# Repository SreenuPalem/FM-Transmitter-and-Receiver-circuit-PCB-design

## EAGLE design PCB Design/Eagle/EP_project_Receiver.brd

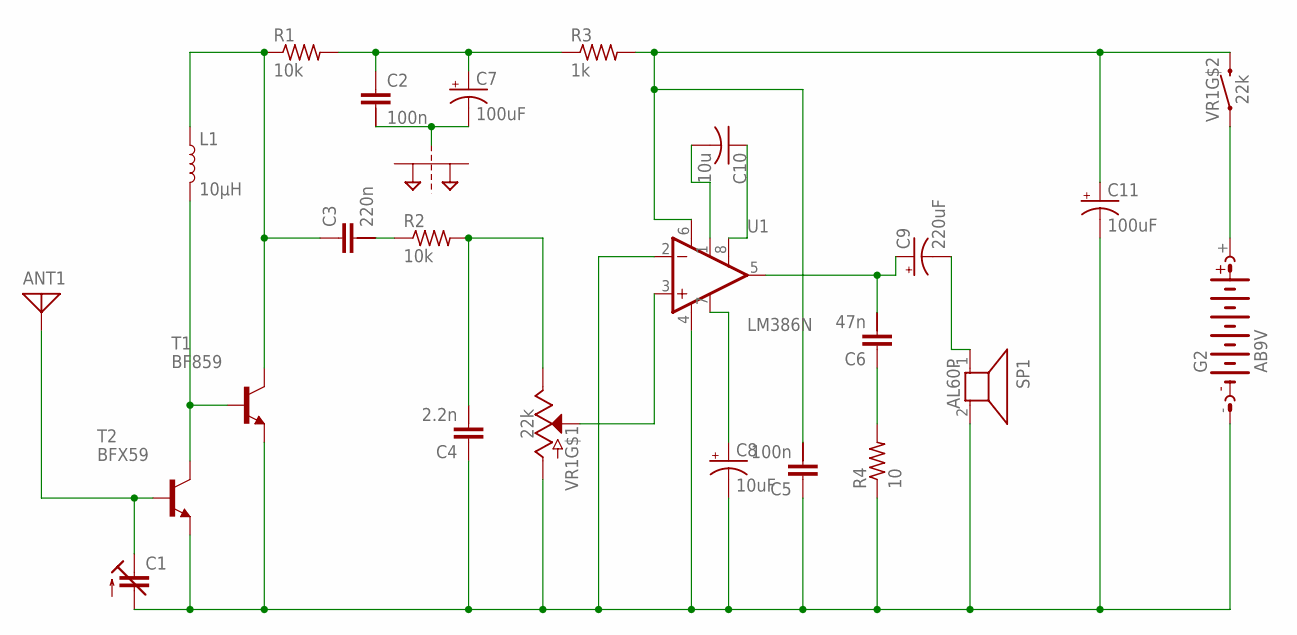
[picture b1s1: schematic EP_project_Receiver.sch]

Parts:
ANT1: ANTENNA; PAD-01
C1: C-TRIMM808; CTRIM808-BC
C2, C5: 100n; C2.5/5-5
C3: 220n; C2.5/5-5
C4: 2.2n; C2.5/5-5
C6: 47n; C2.5/5-5
C7, C11: 100uF; PANASONIC_G
C8: 10uF; PANASONIC_G
C9: 220uF; PANASONIC_G
C10: 10u; C025-024X044
G2: AB9V
L1: 10μH; 0805
R1, R2: 10k; 0204/7
R3: 1k; 0204/7
R4: 10; 0204/7
SP1: AL60P
SUPPLYTIE1: 2PT_GND_TIE
T1: BF859; TO202
T2: BFX59; TO72
U1: LM386N; DIP08
VR1: 22k; POT-SWITCH-PTH

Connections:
unnamed: ANT1.1, C1.1 (E), T2.2 (B)
unnamed: L1.2, T1.3 (B), T2.3 (C)
unnamed: C3.1, L1.1, R1.1, T1.2 (C)
unnamed: C3.2, R2.1
unnamed: C4.2, R2.2, VR1.3 (E)
unnamed: C1.2 (A), C4.1, C5.1, C8.-, C11.-, G2.-, R4.1, SP1.2, T1.1 (E), T2.1 (E), U1.2 (-IN), U1.4 (V-), VR1.1 (A)
unnamed: U1.3 (+IN), VR1.2 (S)
unnamed: C9.-, SP1.1
unnamed: C2.1, C7.+, R1.2, R3.1
unnamed: C2.2, C7.-
unnamed: C5.2, C11.+, R3.2, U1.6 (V+), VR1.S2 (2)
unnamed: G2.+, VR1.S1 (1)
unnamed: C6.1, R4.2
unnamed: C6.2, C9.+, U1.5 (OUT)
unnamed: C8.+, U1.7 (BP)
unnamed: C10.1, U1.8 (GAIN)
unnamed: C10.2, U1.1 (GAIN)

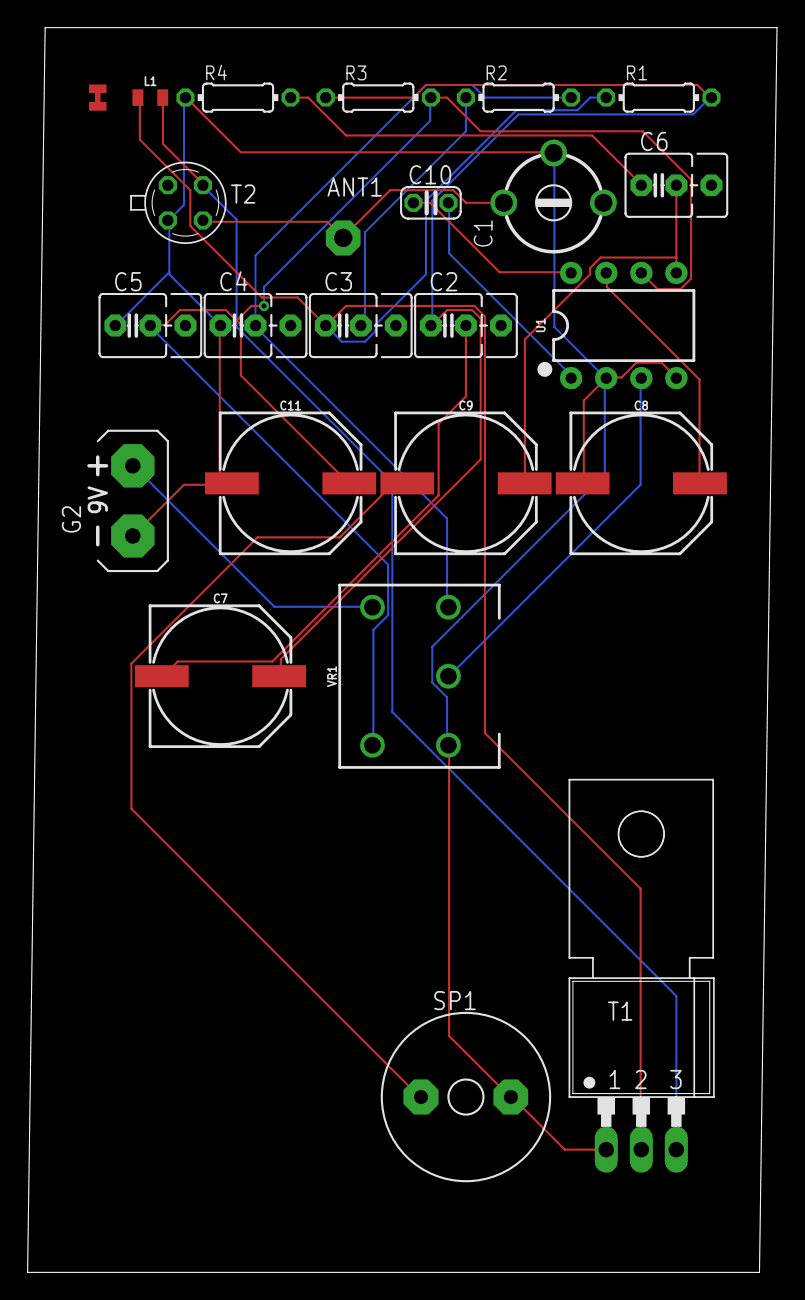
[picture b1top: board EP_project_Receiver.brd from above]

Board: 2 copper layers, 54.3 x 90.2 mm, 24 parts (0 on the bottom side), 17 nets.

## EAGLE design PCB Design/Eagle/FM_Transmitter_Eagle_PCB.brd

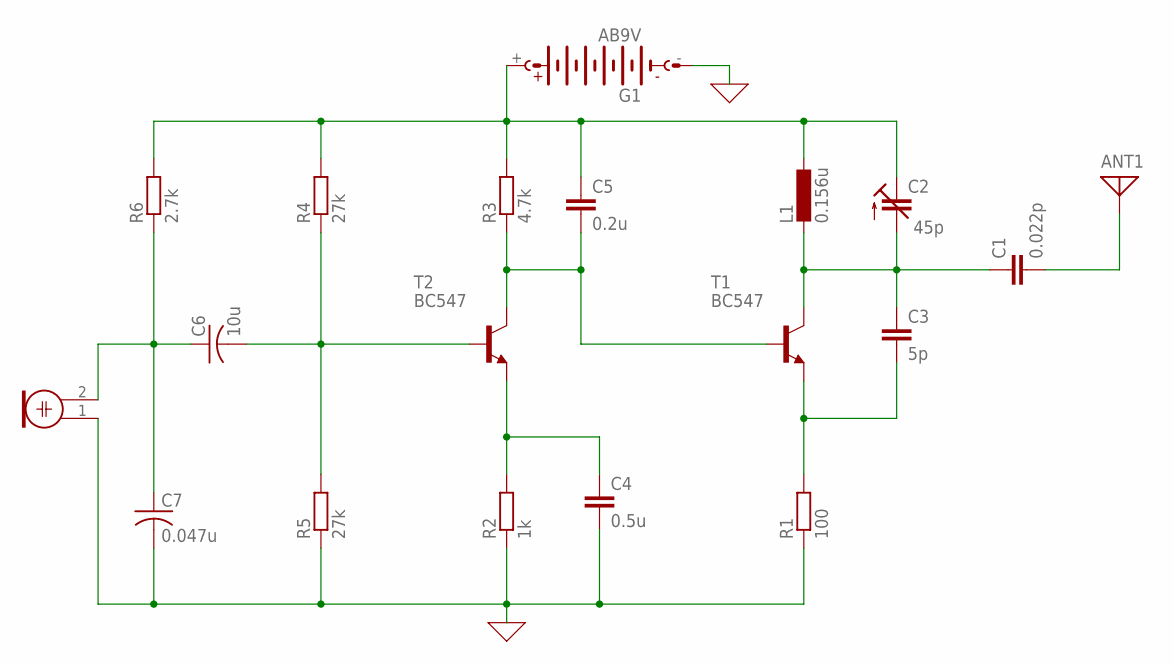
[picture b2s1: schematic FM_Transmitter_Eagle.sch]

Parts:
ANT1: ANTENNA; PAD-01
C1: 0.022p; C025-024X044
C2: 45p; CTRIM808-BC
C3: 5p; C025-024X044
C4: 0.5u; C025-024X044
C5: 0.2u; C025-024X044
C6: 10u; C025-024X044
C7: 0.047u; C025-024X044
G1: AB9V
L1: 0.156u; 0204/5
M1: ELECTRET_MICROPHON-F6050AP; F6050AP
R1: 100; 0204/7
R2: 1k; 0204/7
R3: 4.7k; 0204/7
R4, R5: 27k; 0204/7
R6: 2.7k; 0204/7
T1, T2: BC547; TO92

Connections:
0: C4.2, C7.2, G1.-, M1.1, R1.1, R2.1, R5.1
unnamed: ANT1.1, C1.2
unnamed: C6.1, C7.1, M1.2, R6.1
unnamed: C1.1, C2.2 (A), C3.1, L1.2, T1.3 (C)
unnamed: C3.2, R1.2, T1.1 (E)
unnamed: C4.1, R2.2, T2.1 (E)
unnamed: C5.2, R3.1, T1.2 (B), T2.3 (C)
unnamed: C6.2, R4.1, R5.2, T2.2 (B)
unnamed: C2.1 (E), C5.1, G1.+, L1.1, R3.2, R4.2, R6.2

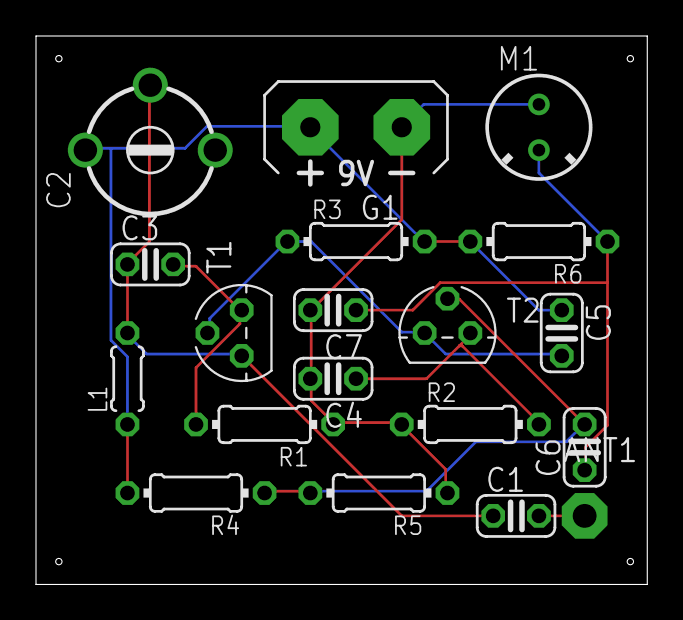
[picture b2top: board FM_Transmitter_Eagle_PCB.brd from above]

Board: 2 copper layers, 34.0 x 30.5 mm, 19 parts (0 on the bottom side), 9 nets.

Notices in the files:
parts and their libraries:
SparkFun-Capacitors: Licensing: Creative Commons ShareAlike 4.0 International - https://creativecommons.org/licenses/by-sa/4.0
